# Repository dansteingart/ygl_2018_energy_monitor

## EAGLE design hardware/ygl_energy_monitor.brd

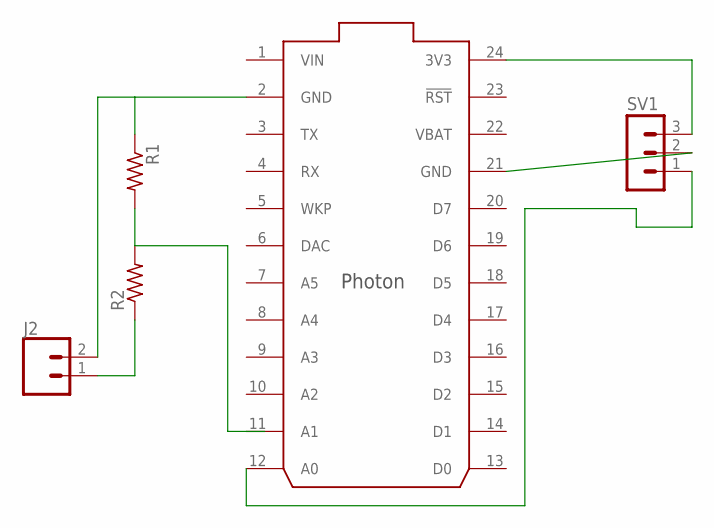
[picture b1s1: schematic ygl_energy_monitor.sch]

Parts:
J2: CONN_023.5MM; SCREWTERMINAL-3.5MM-2
R1, R2: R-US_0207/10; 0207/10
SV1: MA03-1
U$1: PHOTON_WITH_HEADERS; PHOTON

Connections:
unnamed: SV1.3, U$1.24 (3V3)
unnamed: SV1.2, U$1.21 (GND)
unnamed: SV1.1, U$1.12 (A0)
unnamed: J2.2, R1.1, U$1.2 (GND)
unnamed: J2.1, R2.1
unnamed: R1.2, R2.2, U$1.11 (A1)
VBAT: U$1.22 (VBAT)
VIN: U$1.1 (VIN)

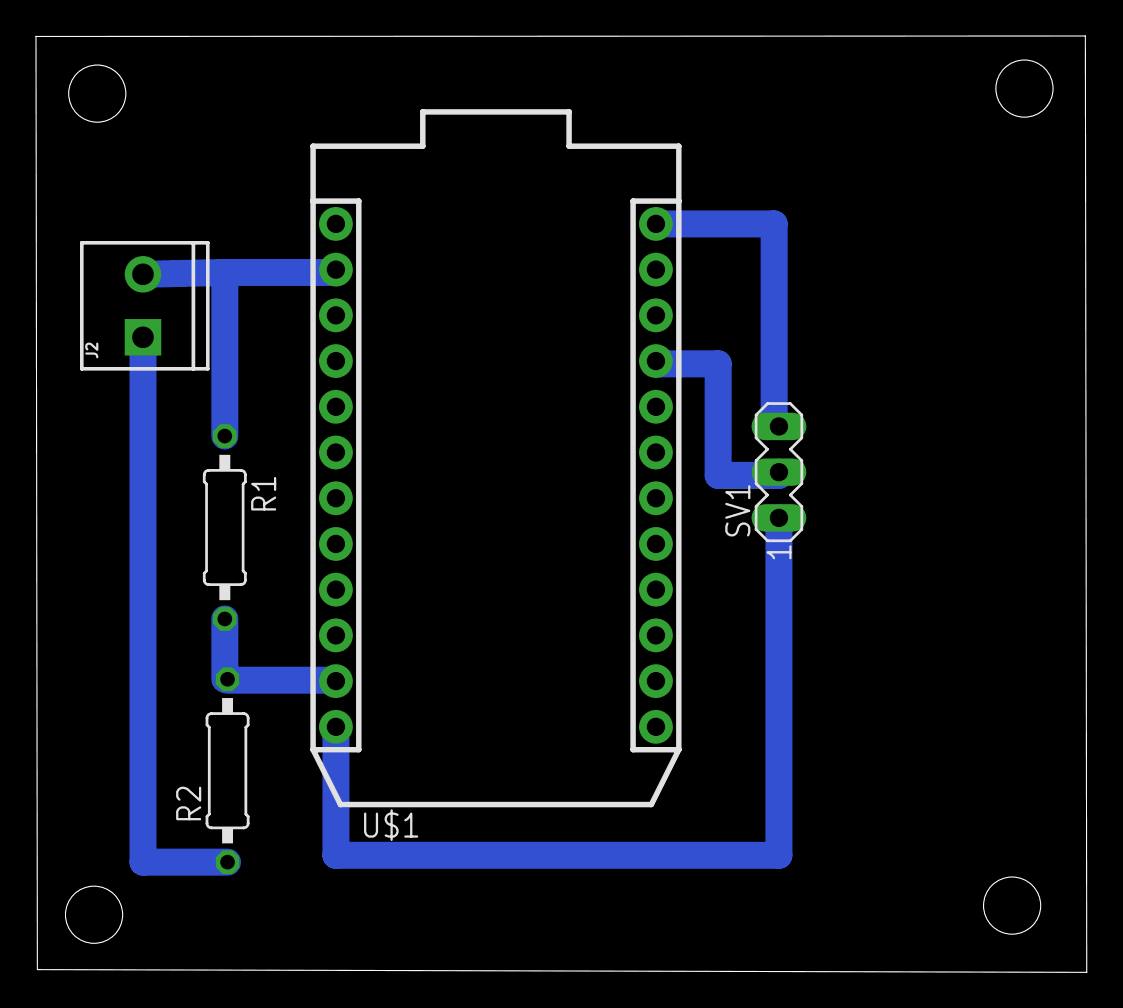
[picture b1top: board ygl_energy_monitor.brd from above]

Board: 2 copper layers, 58.4 x 52.0 mm, 5 parts (0 on the bottom side), 6 nets.

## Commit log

2018-07-13 igngores
2018-07-13 remove extra
2018-07-13 fixed package
2018-07-14 avoid the braze?
2018-07-14 embrace the braze!
2018-07-14 fuck braze!
2018-07-14 header swap

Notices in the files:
parts and their libraries:
SparkFun-Connectors: Licensing: Creative Commons ShareAlike 4.0 International - https://creativecommons.org/licenses/by-sa/4.0
